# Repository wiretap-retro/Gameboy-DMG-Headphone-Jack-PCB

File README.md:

# Gameboy DMG Headphone Jack PCB
A replacement Gameboy DMG headphone jack PCB utilizing all newly manufactured parts -- yes, even the jack.

\

## Intro
To start off, one of my orginal Gameboys has headphone jack issues, and no amount of cleaning fixed it. I tried every YouTube tutorial, forum advice, Discord advice, etc. Surely, someone has to have made a near OEM style replacement right? I guess not. Every replacement board I could find uses the old Gameboy DMG headphone jack. I did find one completely new design in the Super DMG 01, but that strays too far from OEM and has a lot of unnecessary parts if you just want a cheap and simple replacement. I also added a "pro audio" version recently. \
\
After work one day, I decided to take a look at what made people keep using the original corroding jacks on replacement boards. Was it the size / form factor of finding the right replacement? Maybe. Was it confusing to figure out? Apparently. I found all sorts of weird pinouts people tried to draw, people claiming the audio was looping through the jack and back to the speaker, and arguing back and forth over drawing diagrams of how it works. It even confused me, because some people claimed to be confidently correct, then would be proven wrong by someone else. I decided to step back and look at the original Gameboy DMG schematic. After looking at the schematic, it only took about 30 seconds to figure out. But are modern day parts available for the solution? After a brief search on Mouser, it turns out yes.

## How It Works
Looking at the original Gameboy DMG schematic, we're really only interested in the "headphone jack" section as pictured below.
\
\

\
\
Here, it shows there's a switch going to ground that is controlled by the tip switch. Nintendo made this schematic simplified compared to the actual jack, so think of it as a separate single pole switch. It does not work in the same way as a normal tip or ring switch on most headphone jacks. It acts more like a SPST isolated switch, telling the "detect" pin to short to ground or not. This is a normally closed contact, so when it is grounded, the speaker functions. When it is an open contact (ungrounded), the speaker turns off and the headphones function. The control for the detect line is done on the DMG motherboard in the audio amplifier. This is key to be able to duplicate this function properly. A simple tip or ring switchable headphone jack won't perform the detect pin --> ground switching properly without additional circuitry. I think this is where everyone got confused, or couldn't find the right parts.
\
\
Enter the CUI SJ-3566AN 3.5mm headphone jack. This is a special kind of jack that isn't used widely, but still exists for certain applications. It has an isolated SPDT switch controlled by the tip switch, which will allow us to do the proper detect pin --> ground switching we need. 
\
\
Below shows my KiCAD schematic for how it works. You'll notice the CUI headphone jack has pins 4, 5, and 6 as an internal switch. With the headphones unplugged, only pins 4 and 5 are shorted. With the headphones plugged in, only pins 5 and 6 are shorted. The Gameboy DMG shorts detect and ground to activate the speaker, and an open connection on detect and ground to have audio go to the headphones. I simply utilized this  switch to accomplish the switching. You could use other methods or additional chips to do it, but it would likely add complexity, cost, and extra build time.
\
\

## But NOS Still Exists!
I have recently tried that, which inspired this project. I'm not saying all new old stock items are bad, but they are degrading through means of oxidation depending on their storage environment. Even a brand new product sitting on the shelf for 30+ years degrades. I deal with this at work all the time. Metal contacts oxidize, electrolytic capacitors dry up or need to be reformed periodically, and PCBs can delaminate. Here's a few pictures of what I recently encountered. 
\
\
Order slip:
\
\

\
\
Brand new part out of the anti-static bag. Notice the oxidation on the metal in the headphone jack:
\
\

\
\
I cleaned it and tried all the tricks. DeoxIT spray first, Goldwipes between the contacts second, vinegar soak third, and sandpaper between the contacts fourth. It still wouldn't work. I tried sandpaper last, since that should only be used as a last resort. Sandpaper removes the surface plating which normally would be used to make a good electrical contact. However, the oxidation seems to have ate away that good plated surface long ago.
\
\

\
\
If these are truly "new old stock", you can't fault the seller unless they install and test them -- but then they would be a used item, not a new old stock item. Unfortunately, this is what you have to deal with when purchasing decades old parts. This project's goal is to eliminate the need to rely on the decay of new old stock parts, or the frustration of trying to refurbish your existing headphone jack.

## Build Notes
I ordered my PCBs with 1.0mm thickness from JLCPCB. I'm not 100% sure if this is necessary, but I wanted to have extra headroom inside the Gameboy shell just to be sure it would fit. After you're done soldering the headphone jack and 4-pin cable, trim any excess protruding metal/solder off with side cutters to prevent impact with the top of the shell when it is assembled. 
\
\
In the repository, I have included a BOM Excel file. There's a link to my Mouser cart for the parts inside.

## Internal Case Mod Necessary / Installation Pictures
One mod is necessary to make this fit, because the headphone jack itself is larger than the original. I tried to find a smaller jack unsuccessfully. You'll need to cut away the old "walls" that went around the old headphone jack body. This will allow the new CUI SJ-3566AN to fit since it is a few millimeters larger. I used a pair of small side cutters. Leave the screw mounting holes in place, as you'll need them to screw the PCB down to. Be careful and don't cut too far (like I did) where you cut into the screw hole. It would be best to cut away the majority of the "walls", then use a small file to get the rest of the plastic around the screw holes.
\
\

\
\
And here's what it should look like screwed in place. Don't overtighten the screws, because there's a gap when it is tightened down all the way. Just make them snug to the point where the board doesn't move, but isn't flexing. You could also 3D print some small washers to fit between the PCB and screw holes if you'd like. 
\
\

\
\
Due to the OEM Gameboy DMG headphone jack having an offset of roughly 1mm and the new CUI jack not having an offset, it will fit closer to the left side of the external 3.5mm shell opening. Luckily there's enough room and no more case cutting is required. All my headphones still fit in the hole just fine. Grr, OCD problems.
\
\

## Pro Version
The Pro version adds another 3.5mm headphone jack to provide "pro audio", a non-amplified left and right audio channel to run into a mixer or other equipment. This is normally used with a 3.5mm to RCA cable. The installation is the same as the original version above, except you need to make an additional cutout on the shell to allow the other 3.5mm jack to come through. 
\
\
This mod does not require cutting of the original 4-pin harness, and you can use both jacks simultaneously if desired. You will need to run two additional wires to the PCB from the volume potentiometer. See diagram below for the Right and Left pre-out solder points to connect to the pro audio PCB.
\
\

## Closing Thoughts
This was a pretty fun project and I hope it helps out the community. As the supply of good/working original headphone jacks dwindle, we needed a solution like this to keep these handhelds alive. I tried to keep this one similar to OEM, but with updated parts. Feel free to utilize my design for your work, but please give me credit in your inspired works for figuring out this core design. Build and sell these if you want to make a few bucks along the way. Thanks!

Discussion: [My Reddit Post](https://www.reddit.com/r/Gameboy/comments/1aojew2/gameboy_dmg_headphone_jack_replacement/)

## Revision History
Rev 0 Pro - Initial revision.
\
Rev 0 - Initial revision. Tested and working, good to build.

## License
This project is licensed under Creative Commons Legal Code CC0 1.0 Universal. Please view the LICENSE file in this Github Repository.

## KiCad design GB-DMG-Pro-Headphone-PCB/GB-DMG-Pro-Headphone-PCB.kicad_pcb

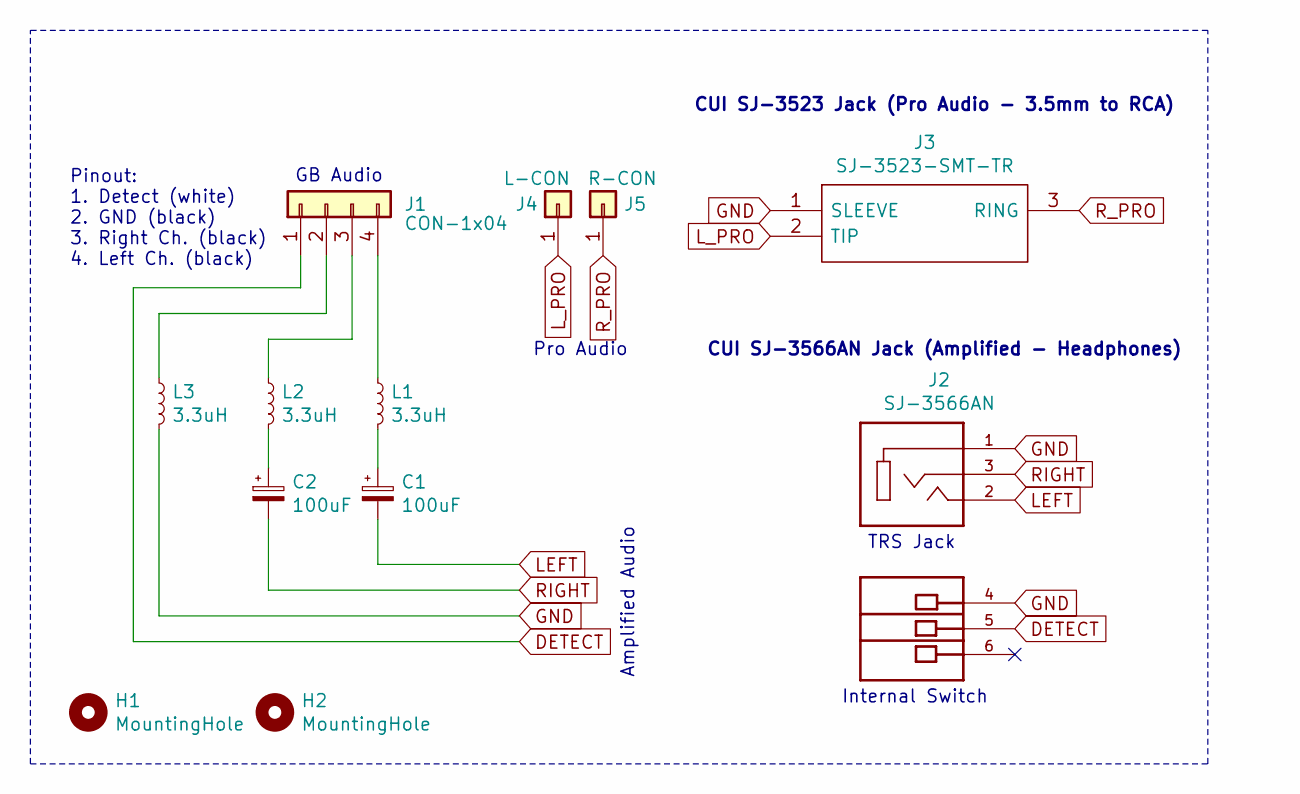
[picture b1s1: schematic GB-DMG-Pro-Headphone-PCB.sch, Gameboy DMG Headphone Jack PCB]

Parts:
C1, C2: 100uF; CAPAE530X550N; Manufacturer_Part_Number 865080142007; Mouser Part Number 710-865080142007
H1, H2: MountingHole; MountingHole_2.2mm_M2
J1: CON-1x04; PinHeader_1x04_P2.54mm_Vertical
J2: SJ-3566AN; CUI_SJ-3566AN; Manufacturer_Part_Number SJ-3566AN; Mouser Part Number 490-SJ-3566AN
J3: SJ-3523-SMT-TR; SJ3523SMTTR; Mouser Part Number 490-SJ-3523-SMT-TR
J4: L-CON; TestPoint_THTPad_1.5x1.5mm_Drill0.7mm
J5: R-CON; TestPoint_THTPad_1.5x1.5mm_Drill0.7mm
L1, L2, L3: 3.3uH; L_0805_2012Metric_Pad1.15x1.40mm_HandSolder; Manufacturer_Part_Number LQM21PH3R3XGEL80; Mouser Part Number 81-LQM21PH3R3XGEL80

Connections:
DETECT: J1.1, J2.5
GND: J2.1, J2.4, J3.1 (SLEEVE), L3.2
LEFT: C1.2, J2.2
L_PRO: J3.2 (TIP), J4.1
unnamed: C1.1, L1.2
unnamed: C2.1, L2.2
unnamed: J1.2, L3.1
unnamed: J1.3, L2.1
unnamed: J1.4, L1.1
RIGHT: C2.2, J2.3
R_PRO: J3.3 (RING), J5.1

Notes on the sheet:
GB Audio
Pinout: 1. Detect (white) 2. GND (black) 3. Right Ch. (black) 4. Left Ch. (black)
CUI SJ-3566AN Jack (Amplified - Headphones)
TRS Jack
Internal Switch
CUI SJ-3523 Jack (Pro Audio - 3.5mm to RCA)
Pro Audio
Amplified Audio

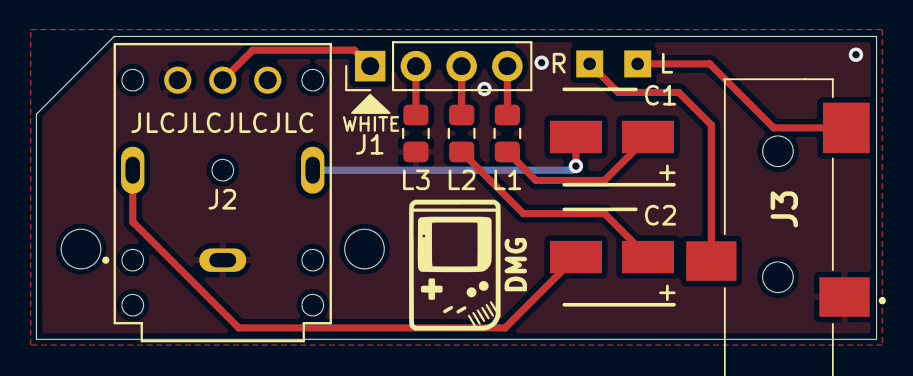
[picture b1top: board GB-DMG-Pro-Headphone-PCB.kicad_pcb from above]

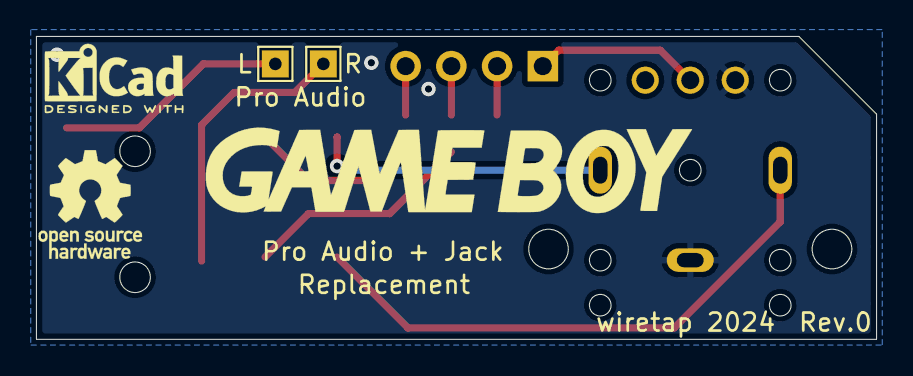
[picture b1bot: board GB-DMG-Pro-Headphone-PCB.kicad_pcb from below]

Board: 2 copper layers, 46.7 x 16.8 mm, 12 parts (2 on the bottom side), 11 nets.

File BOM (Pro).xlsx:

Reference | Quantity | Value | Footprint | Manufacturer | Part Number | Mouser Part Number
C1, C2 | 2 | 100uF | CAPAE530X550N | Wurth Elektronik | 865080142007 | 710-865080142007
J2 | 1 | SJ-3566AN | CUI_SJ-3566AN | CUI Inc | SJ-3566AN | 490-SJ-3566AN
J3 | 1 | SJ-3523 | SJ3523SMTTR | CUI Inc | SJ-3523-SMT-TR | 490-SJ-3523-SMT-TR
L1, L2, L3 | 3 | 3.3uH | 0805 | Murata Electronics | LQM21PH3R3XGEL80 | 81-LQM21PH3R3XGEL80
Mouser Cart Link
Click!
Recommended:
Order PCB with 1mm Thickness

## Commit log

2024-02-19 Added Pro Audio version

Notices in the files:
GB-DMG-Pro-Headphone-PCB/GB-DMG-Pro-Headphone-PCB.kicad_pcb:
License: Creative Commons Zero v1.0 Universal
